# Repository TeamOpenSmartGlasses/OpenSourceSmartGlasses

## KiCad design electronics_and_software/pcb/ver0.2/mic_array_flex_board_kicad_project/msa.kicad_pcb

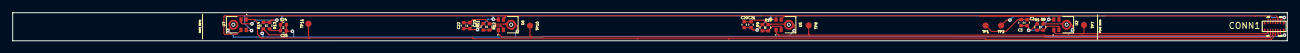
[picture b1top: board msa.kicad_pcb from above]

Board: 2 copper layers, 206.5 x 4.6 mm, 27 parts (0 on the bottom side), 11 nets.

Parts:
C2, C20, C22, C24: 0.1uF; C_0402_1005Metric
C3, C21, C23, C25: 1uF; C_0402_1005Metric
CONN1: slim_stack_12pos_5035521222_schematic; slim_stack_molex_PLUG_5035521222
R1, R8, R9, R10, R11, R12, R13, R14: 10K; R_0402_1005Metric
TP1, TP2, TP7, TP8, TP10, TP11: TestPoint; SMD_1x01_P1.27mm
U2, U5, U6, U7: MP23DB01HPTR; MIC_SPH0641LU4H-1

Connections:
+3V3: C2.2, C3.2, C20.2, C21.2, C22.2, C23.2, C24.2, C25.2, CONN1.6, R1.1, R9.1, R11.1, R13.1, TP2.1, U2.5 (VDD), U5.5 (VDD), U6.5 (VDD), U7.5 (VDD)
/MIC_CLK: CONN1.5, U2.4 (CLK), U5.4 (CLK), U6.4 (CLK), U7.4 (CLK)
/MIC_DOUT_0: CONN1.7, TP7.1, U2.1 (DOUT)
/MIC_DOUT_1: CONN1.8, TP8.1, U5.1 (DOUT)
/MIC_DOUT_2: CONN1.9, TP10.1, U6.1 (DOUT)
/MIC_DOUT_3: CONN1.10, TP11.1, U7.1 (DOUT)
GND: C2.1, C3.1, C20.1, C21.1, C22.1, C23.1, C24.1, C25.1, CONN1.11, R8.2, R10.2, R12.2, R14.2, TP1.1, U2.3 (GND), U5.3 (GND), U6.3 (GND), U7.3 (GND)
unnamed: R1.2, R8.1, U2.2 (L/R)
unnamed: R9.2, R10.1, U5.2 (L/R)
unnamed: R11.2, R12.1, U6.2 (L/R)
unnamed: R13.2, R14.1, U7.2 (L/R)
